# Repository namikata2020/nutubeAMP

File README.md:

# Audio amplifier using a Nutube 6P1

株式会社コルグ(KORG)が開発した真空管Nutube 6P1を使用したオーディオアンプです。出力段はトランジスタを使用しています。
出力は5W程度です。

### 回路図

### プリント基板

[kicad](https://kicad.org/)で作成した回路図データです。

## 参考
[21世紀時代の真空管 Nutube でヘッドホンアンプを作ってみた！](http://www.maroon.dti.ne.jp/jyaku9/electronic/electronic5/electronic5-1.html)

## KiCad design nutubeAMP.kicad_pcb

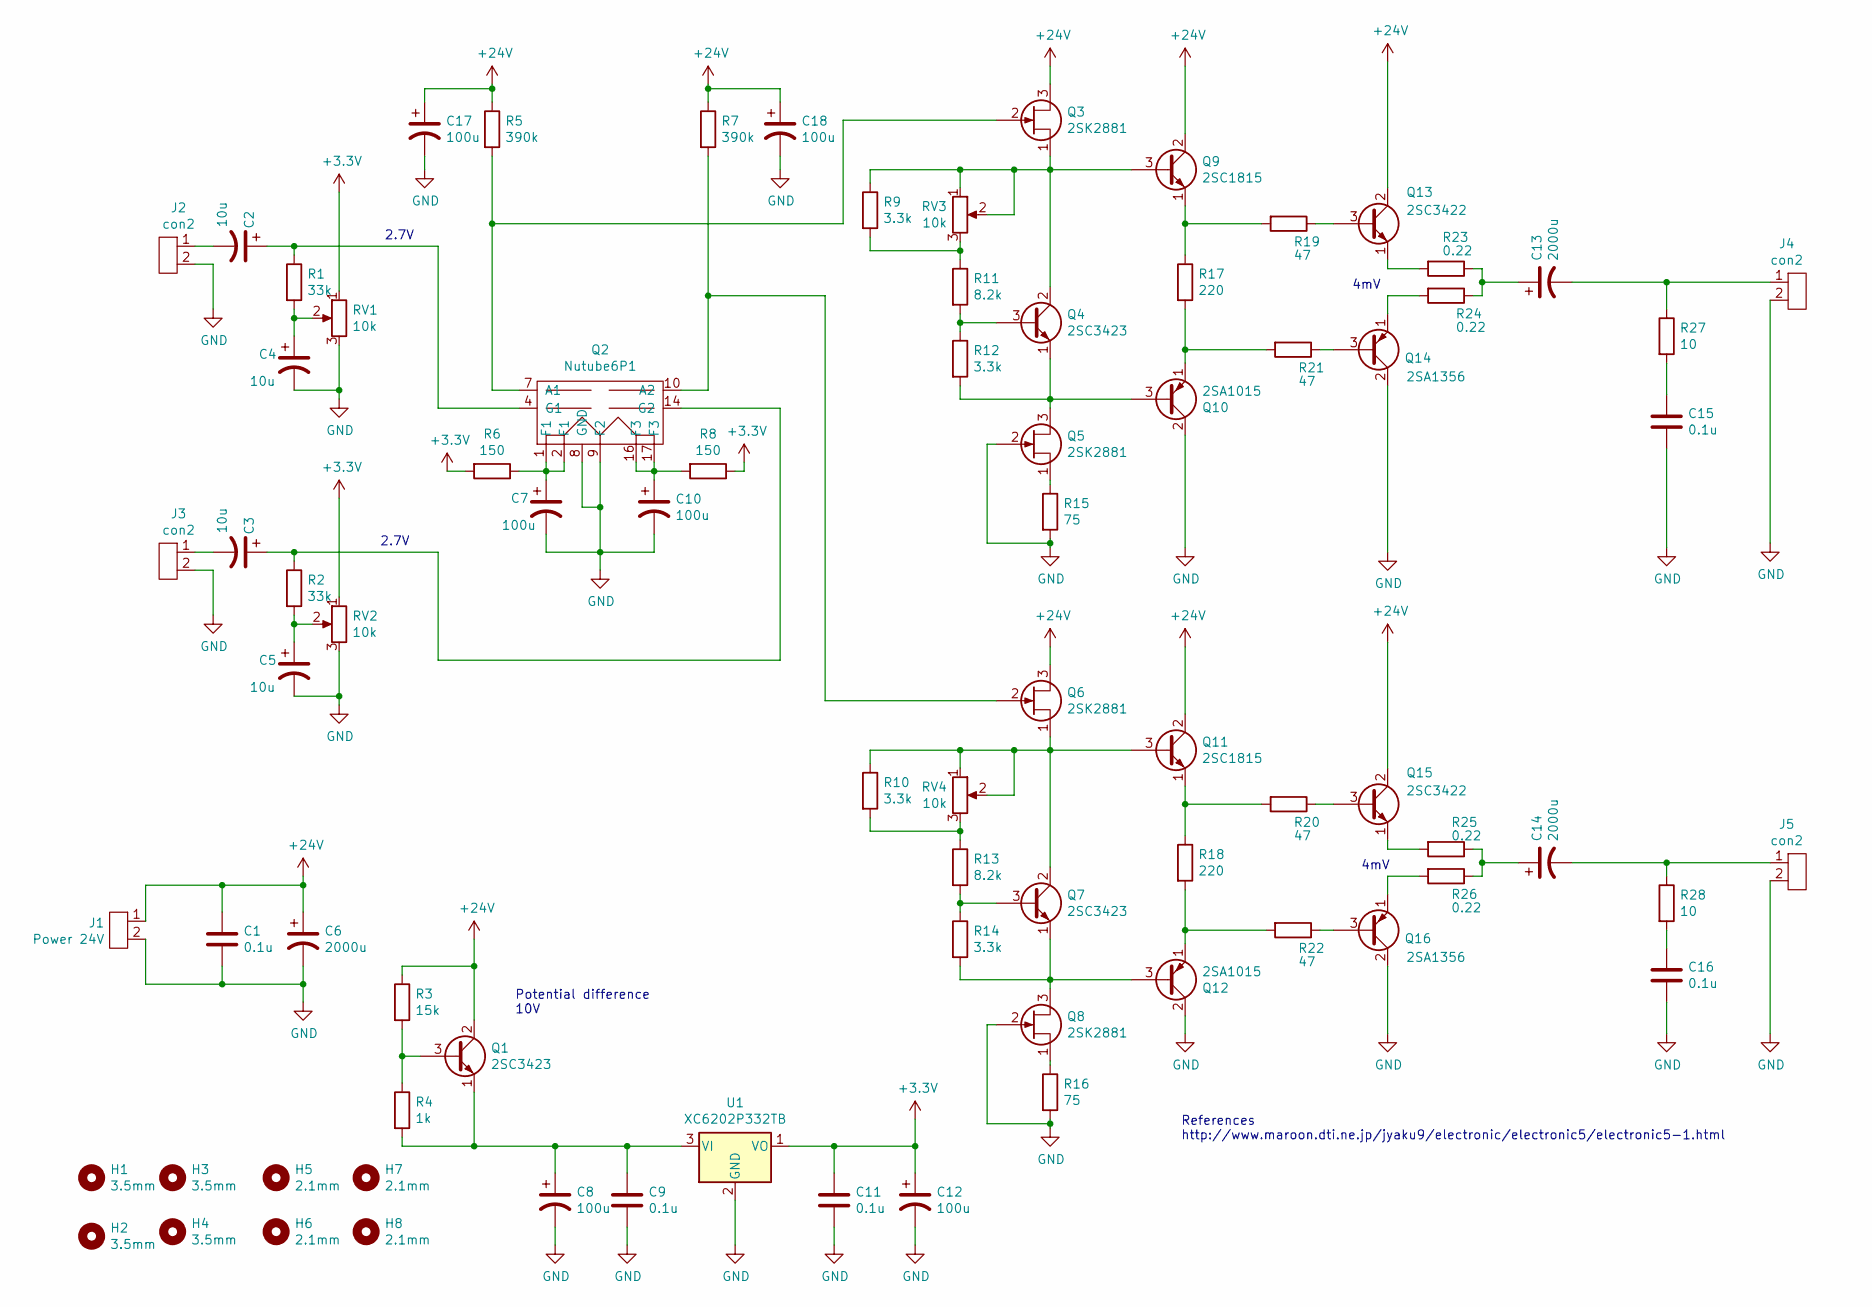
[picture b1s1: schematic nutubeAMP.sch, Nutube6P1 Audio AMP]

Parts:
C1, C9, C11, C15, C16: 0.1u; C_Disc_D5.0mm_W2.5mm_P5.00mm
C2, C3, C4, C5: 10u; CP_Radial_D5.0mm_P2.00mm
C6, C13, C14: 2000u; CP_Radial_D16.0mm_P7.50mm
C7, C8, C10, C12, C17, C18: 100u; CP_Radial_D5.0mm_P2.00mm
H1, H2, H3, H4: 3.5mm; MountingHole_3.2mm_M3
H5, H6, H7, H8: 2.1mm; MountingHole_2.1mm
J1: Power 24V; PhoenixContact_MCV_1,5_2-G-5.08_1x02_P5.08mm_Vertical
J2, J3, J4, J5: con2; PhoenixContact_MCV_1,5_2-G-5.08_1x02_P5.08mm_Vertical
Q1, Q4, Q7: 2SC3423; TO-126-3_Vertical
Q2: Nutube6P1; nutube6p1
Q3, Q5, Q6, Q8: 2SK2881; TO-92S_Wide
Q9, Q11: 2SC1815; TO-92_Inline_Wide
Q10, Q12: 2SA1015; TO-92_Inline_Wide
Q13, Q15: 2SC3422; TO-126-3_Vertical
Q14, Q16: 2SA1356; TO-126-3_Vertical
R1, R2: 33k; R_Axial_DIN0207_L6.3mm_D2.5mm_P10.16mm_Horizontal
R3: 15k; R_Axial_DIN0207_L6.3mm_D2.5mm_P10.16mm_Horizontal
R4: 1k; R_Axial_DIN0207_L6.3mm_D2.5mm_P10.16mm_Horizontal
R5, R7: 390k; R_Axial_DIN0207_L6.3mm_D2.5mm_P10.16mm_Horizontal
R6, R8: 150; R_Axial_DIN0207_L6.3mm_D2.5mm_P10.16mm_Horizontal
R9, R10, R12, R14: 3.3k; R_Axial_DIN0207_L6.3mm_D2.5mm_P10.16mm_Horizontal
R11, R13: 8.2k; R_Axial_DIN0207_L6.3mm_D2.5mm_P10.16mm_Horizontal
R15, R16: 75; R_Axial_DIN0207_L6.3mm_D2.5mm_P10.16mm_Horizontal
R17, R18: 220; R_Axial_DIN0207_L6.3mm_D2.5mm_P10.16mm_Horizontal
R19, R20, R21, R22: 47; R_Axial_DIN0207_L6.3mm_D2.5mm_P10.16mm_Horizontal
R23, R24, R25, R26: 0.22; R_Axial_DIN0516_L15.5mm_D5.0mm_P5.08mm_Vertical
R27, R28: 10; R_Axial_DIN0207_L6.3mm_D2.5mm_P10.16mm_Horizontal
RV1, RV2, RV3, RV4: 10k; Potentiometer_Bourns_3296W_Vertical
U1: XC6202P332TB; TO-92_Inline_Wide

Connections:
+3V3: C11.1, C12.1, R6.2, R8.1, RV1.1, RV2.1, U1.1 (VO)
+24V: C1.1, C6.1, C17.1, C18.1, J1.1, Q1.2 (C), Q3.3 (D), Q6.3 (D), Q9.2 (C), Q11.2 (C), Q13.2 (C), Q15.2 (C), R3.1, R5.1, R7.1
GND: C1.2, C4.2, C5.2, C6.2, C7.2, C8.2, C9.2, C10.2, C11.2, C12.2, C15.2, C16.2, C17.2, C18.2, J1.2, J2.2, J3.2, J4.2, J5.2, Q2.8 (GND), Q2.9 (F2), Q5.2 (G), Q8.2 (G), Q10.2 (C), Q12.2 (C), Q14.2 (C), Q16.2 (C), R15.2, R16.2, RV1.3, RV2.3, U1.2 (GND)
unnamed: C2.1, Q2.4 (G1), R1.1
unnamed: C2.2, J2.1
unnamed: C3.1, Q2.14 (G2), R2.1
unnamed: C3.2, J3.1
unnamed: C4.1, R1.2, RV1.2
unnamed: C5.1, R2.2, RV2.2
unnamed: C7.1, Q2.1 (F1), Q2.2 (F1), R6.1
unnamed: C8.1, C9.1, Q1.1 (E), R4.2, U1.3 (VI)
unnamed: C10.1, Q2.16 (F3), Q2.17 (F3), R8.2
unnamed: C13.1, R23.1, R24.1
unnamed: C13.2, J4.1, R27.1
unnamed: C14.1, R25.1, R26.1
unnamed: C14.2, J5.1, R28.1
unnamed: C15.1, R27.2
unnamed: C16.1, R28.2
unnamed: Q1.3 (B), R3.2, R4.1
unnamed: Q2.7 (A1), Q3.2 (G), R5.2
unnamed: Q2.10 (A2), Q6.2 (G), R7.2
unnamed: Q3.1 (S), Q4.2 (C), Q9.3 (B), R9.1, RV3.1, RV3.2
unnamed: Q4.3 (B), R11.2, R12.1
unnamed: Q5.1 (S), R15.1
unnamed: Q7.3 (B), R13.2, R14.1
unnamed: Q8.1 (S), R16.1
unnamed: Q9.1 (E), R17.1, R19.2
unnamed: Q10.1 (E), R17.2, R21.2
unnamed: Q4.1 (E), Q5.3 (D), Q10.3 (B), R12.2
unnamed: Q11.1 (E), R18.1, R20.2
unnamed: Q6.1 (S), Q7.2 (C), Q11.3 (B), R10.1, RV4.1, RV4.2
unnamed: Q12.1 (E), R18.2, R22.2
unnamed: Q7.1 (E), Q8.3 (D), Q12.3 (B), R14.2
unnamed: Q13.1 (E), R23.2
unnamed: Q13.3 (B), R19.1
unnamed: Q14.1 (E), R24.2
unnamed: Q14.3 (B), R21.1
unnamed: Q15.1 (E), R25.2
unnamed: Q15.3 (B), R20.1
unnamed: Q16.1 (E), R26.2
unnamed: Q16.3 (B), R22.1
unnamed: R10.2, R13.1, RV4.3
unnamed: R9.2, R11.1, RV3.3

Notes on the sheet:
Potential difference 10V
2.7V
4mV
References http://www.maroon.dti.ne.jp/jyaku9/electronic/electronic5/electronic5-1.html

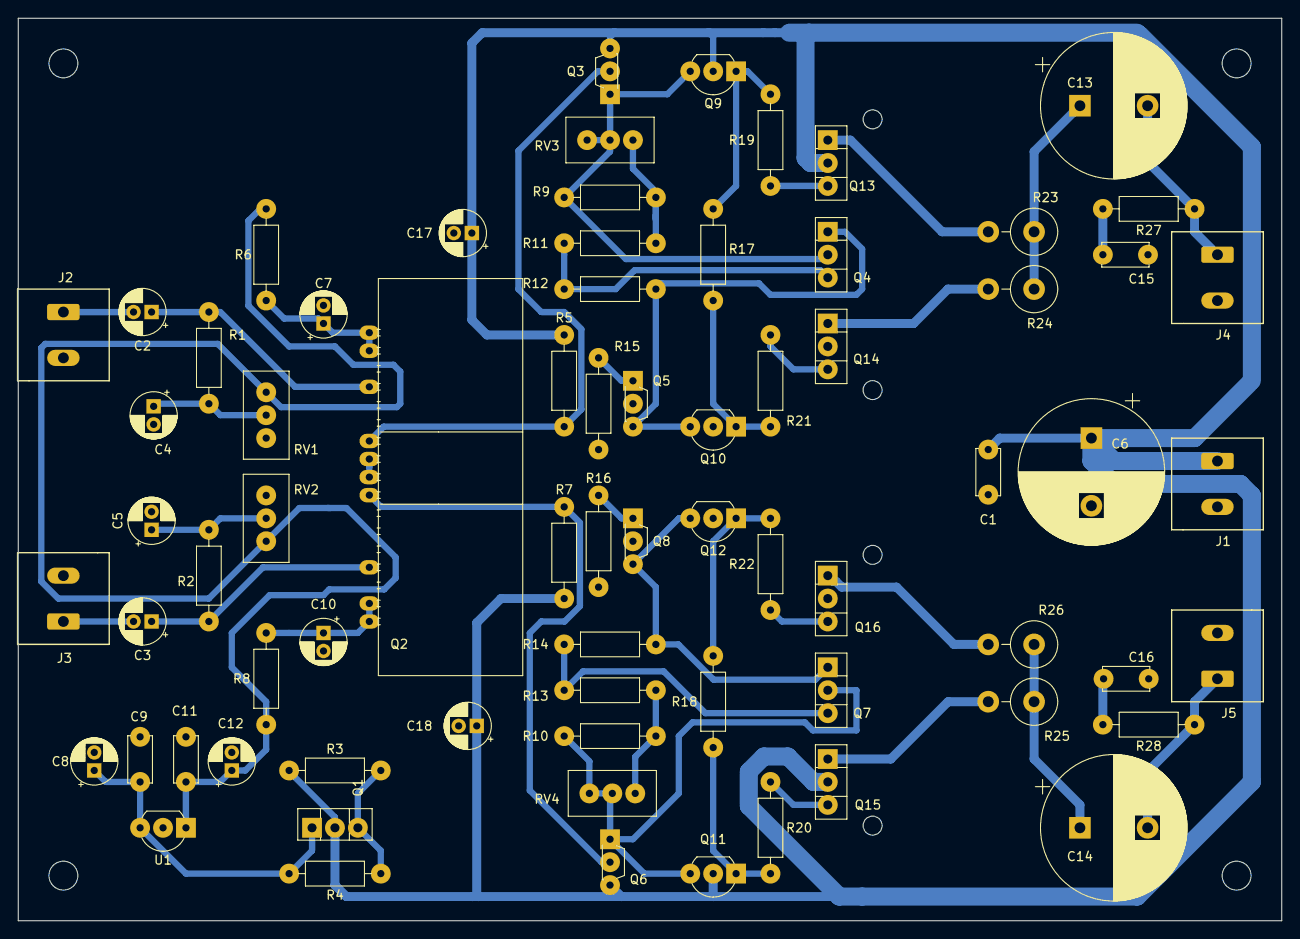
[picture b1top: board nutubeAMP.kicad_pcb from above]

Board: 2 copper layers, 140.0 x 100.0 mm, 80 parts (0 on the bottom side), 43 nets.

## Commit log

2020-11-25 add README
2020-11-25 modify nutubeAMP.png
2020-11-27 rename nutubepho.png
